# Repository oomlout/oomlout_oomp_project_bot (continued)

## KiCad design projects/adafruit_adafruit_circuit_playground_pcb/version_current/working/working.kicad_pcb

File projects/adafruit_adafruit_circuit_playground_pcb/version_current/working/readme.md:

# OOMP Project  
## Adafruit-Circuit-Playground-PCB  by adafruit  
  
oomp key: oomp_projects_flat_adafruit_adafruit_circuit_playground_pcb  
(snippet of original readme)  
  
-- Adafruit Circuit Playground Classic PCB  
<a href="http://www.adafruit.com/products/3000"><br/>  
Click here to purchase one from the Adafruit shop</a>  
  
This is the Classic version of Circuit Playground, which comes with an ATmega32u4. It's designed to be used with Arduino IDE and code.org CS Discoveries only. It even comes with Firmata already programmed in, so you can use it immediately with code.org Discoveries without any preparation or updates.  
  
If you would like to use MakeCode or CircuitPython, check out [Circuit Playground Express](http://www.adafruit.com/products/3333), which can be used with MakeCode, CircuitPython or Arduino.  
  
Circuit Playground features an ATmega32u4 processor, just like our popular Flora. The board's also round and has alligator-clip pads around it so you don't have to solder or sew to make it work. You can power it from USB, a AAA battery pack, or with a Lipoly battery (for advanced users). Just program your code into the board then take it on the go!  
  
This is the PCB files for the Adafruit **Circuit Playground Classic** (not the Express). The format is EagleCAD schematic and board layout  
- http://www.adafruit.com/products/3000  
  
**The Circuit Playground Express can be found at http://www.adafruit.com/products/3333**  
  
--- License  
  
Adafruit invests time and resources providing this open source design, please support Adafruit and open-source hardware by purchasing products from [Adafruit](https://ww  
  full source readme at [readme_src.md](readme_src.md)  
  
source repo at: [https://github.com/adafruit/Adafruit-Circuit-Playground-PCB](https://github.com/adafruit/Adafruit-Circuit-Playground-PCB)  
## Board  

## Schematic  

[schematic pdf](working_schematic.pdf)  
## Images

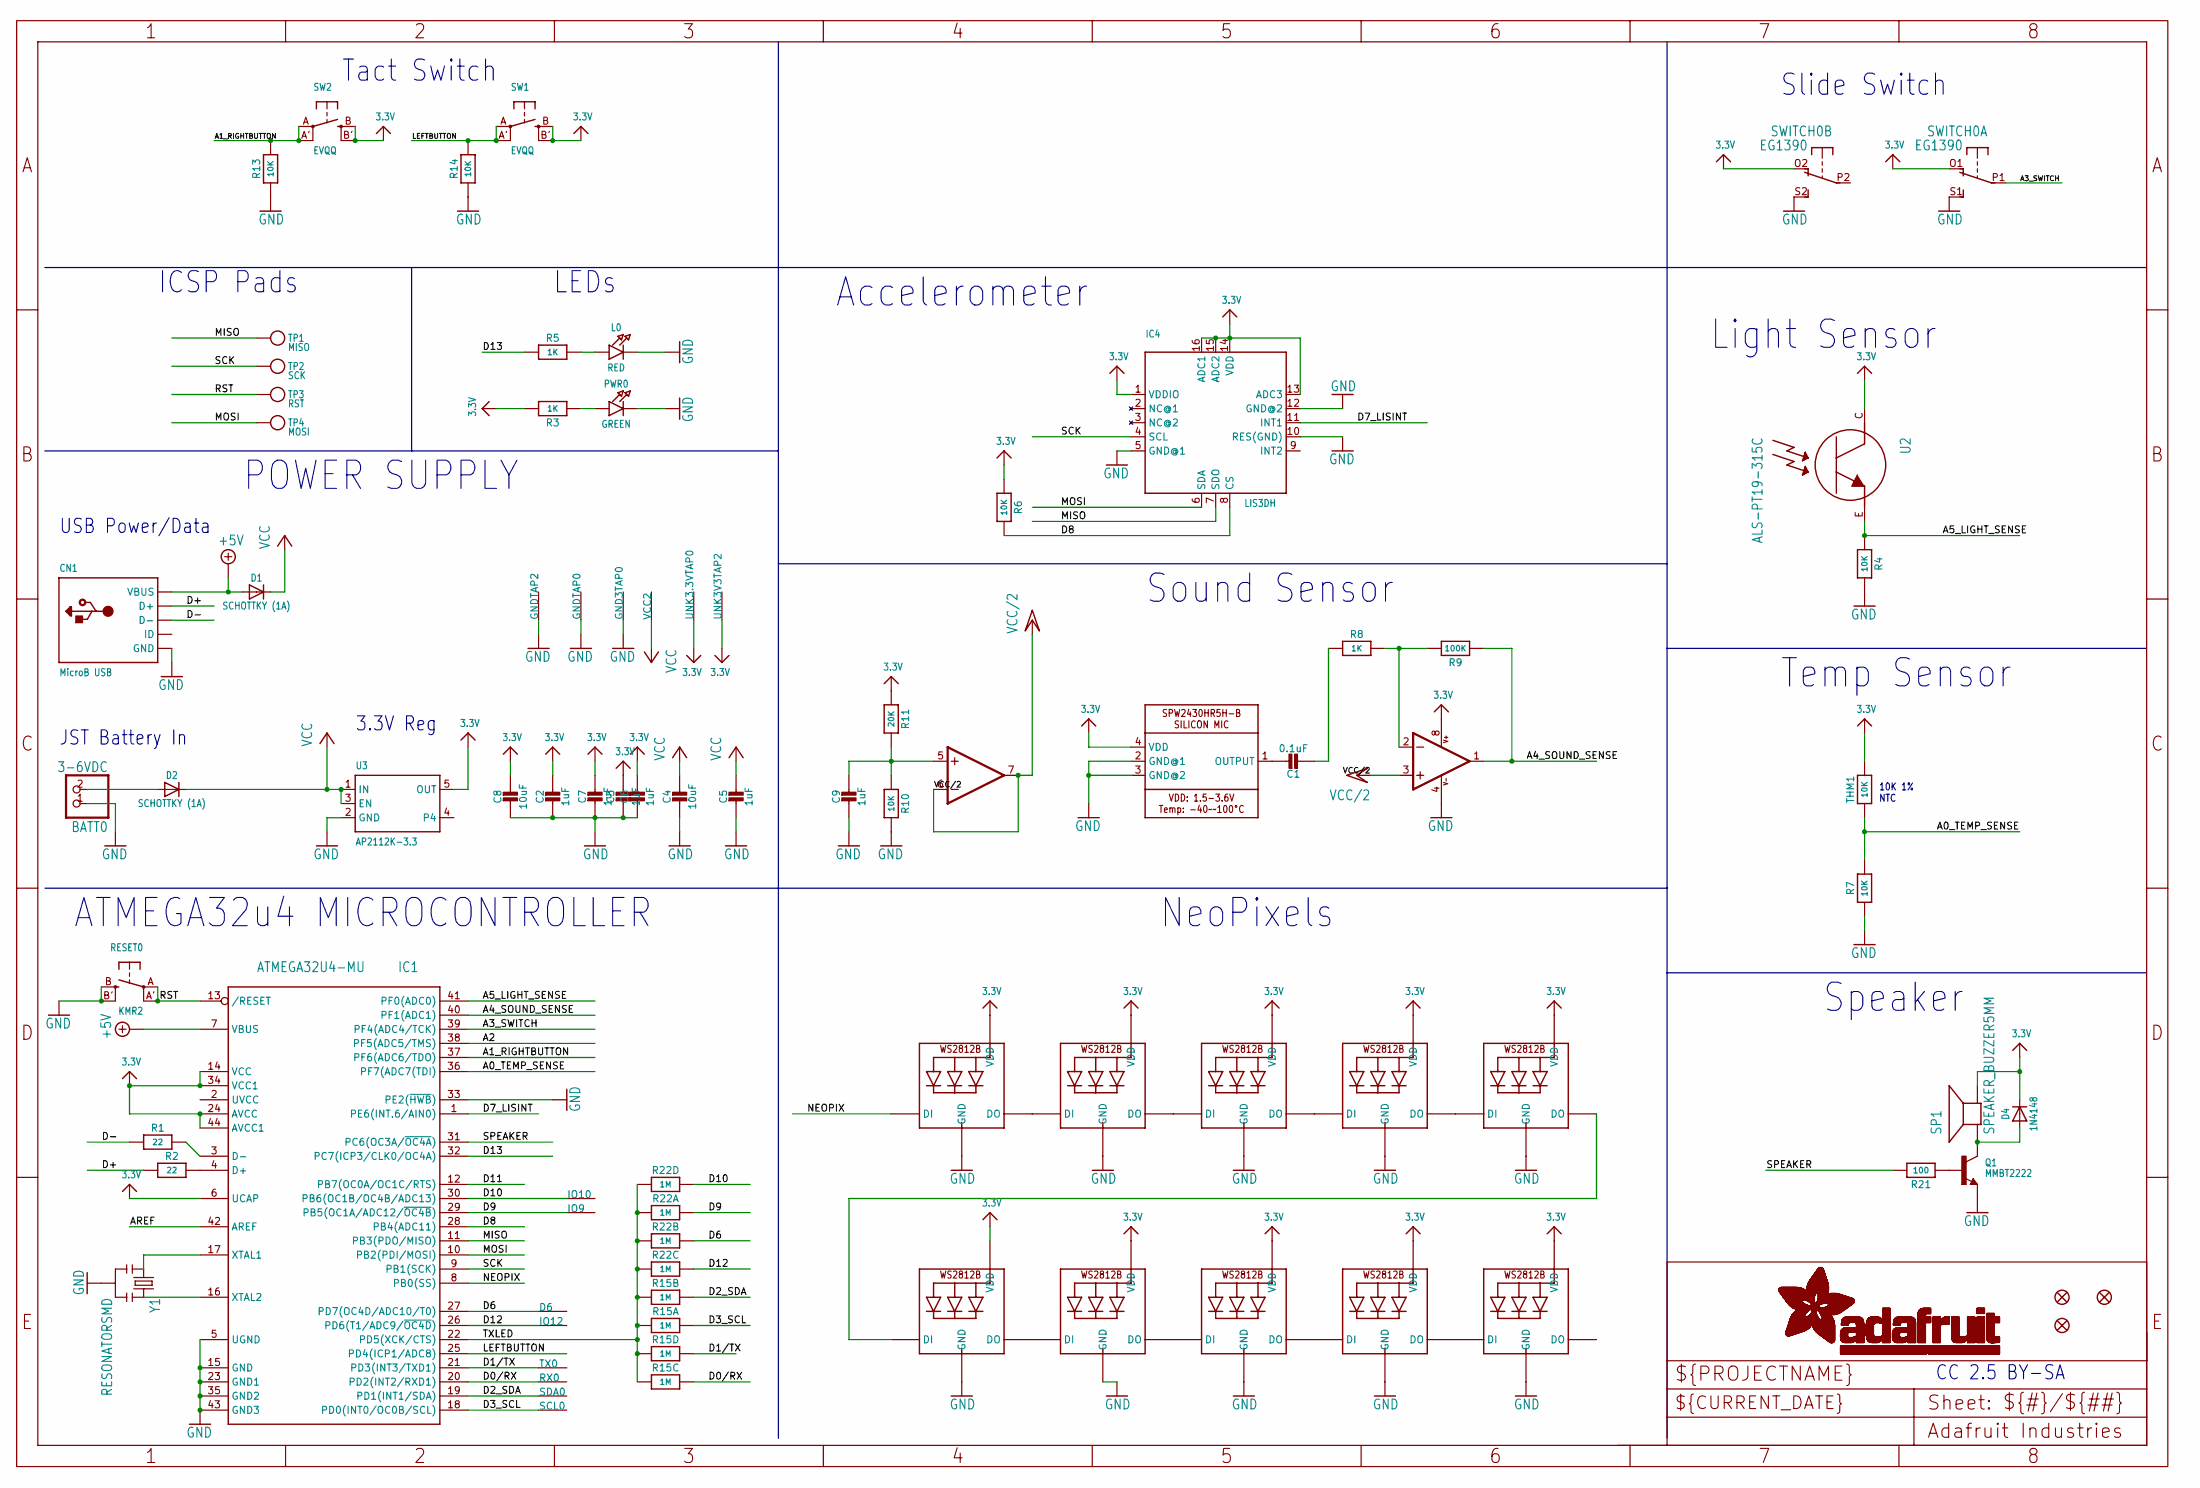
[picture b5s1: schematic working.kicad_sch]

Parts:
BATT0: 3-6VDC; JSTPH2
C1: 0.1uF; 0603-NO
C2, C3, C5, C6, C7, C9: 1uF; 0603-NO
C4, C8: 10uF; 0805-NO
CN1: MicroB USB; 4UCONN_20329_V2
D1, D2: SCHOTTKY (1A); SOD-123
D4: 1N4148; SOD-323
D6: SEWTAP-ALLIGATOR; SEWALLI
GND3TAP0: SEWTAP-ALLIGATOR; SEWALLI
GNDTAP0, GNDTAP2: SEWTAP-ALLIGATOR; SEWALLI
IC1: ATMEGA32U4-MU; TQFN44_7MM
IC2: LMV358?MM; MSOP08
IC4: LIS3DH; LGA16_3X3MM
IO9, IO10, IO12: SEWTAP-ALLIGATOR; SEWALLI
L0: RED; CHIPLED_0805_NOOUTLINE
LED1, LED2, LED3, LED4, LED5, LED6, LED7, LED8, LED9, LED10: WS2812B3535; LED3535
PWR0: GREEN; CHIPLED_0805_NOOUTLINE
Q1: MMBT2222; SOT23-WIDE
R1, R2: 22; 0603-NO
R3, R5, R8: 1K; 0603-NO
R4, R6, R7, R10, R13, R14: 10K; 0603-NO
R9: 100K; 0603-NO
R11: 20K; 0603-NO
R15, R22: 1M; RESPACK_4X0603_NO
R21: 100; 0603-NO
RESET0: KMR2; BTN_KMR2_4.6X2.8
RX0: SEWTAP-ALLIGATOR; SEWALLI
SCL0: SEWTAP-ALLIGATOR; SEWALLI
SDA0: SEWTAP-ALLIGATOR; SEWALLI
SP1: SPEAKER_BUZZER5MM; BUZZER_SMT_5MM
SW1, SW2: EVQQ; EVQ-Q2_SMALLER
SWITCH0: EG1390
THM1: 10K; _0402
TP1: MISO; TESTPOINT_ROUND_1.5MM
TP2: SCK; TESTPOINT_ROUND_1.5MM
TP3: RST; TESTPOINT_ROUND_1.5MM
TP4: MOSI; TESTPOINT_ROUND_1.5MM
TX0: SEWTAP-ALLIGATOR; SEWALLI
U1: SPW2430; SPW2430HR5H-B
U2: ALS-PT19-315C
U3: AP2112K-3.3; SOT23-5
U$2, U$3, U$6: FIDUCIAL""; FIDUCIAL_1MM
UNK3.3VTAP0, UNK3V3TAP2: SEWTAP-ALLIGATOR; SEWALLI
VCC2: SEWTAP-ALLIGATOR; SEWALLI
Y1: RESONATORSMD; RESONATOR-SMD

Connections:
3.3V: C2.1, C3.1, C6.1, C7.1, C8.1, D4.C, IC1.6 (UCAP), IC1.14 (VCC), IC1.24 (AVCC), IC1.34 (VCC1), IC1.44 (AVCC1), IC2.8 (V+), IC4.1 (VDDIO), IC4.13 (ADC3), IC4.14 (VDD), IC4.15 (ADC2), IC4.16 (ADC1), LED1.2 (VDD), LED2.2 (VDD), LED3.2 (VDD), LED4.2 (VDD), LED5.2 (VDD), LED6.2 (VDD), LED7.2 (VDD), LED8.2 (VDD), LED9.2 (VDD), LED10.2 (VDD), R3.2, R6.1, R11.1, SP1.-, SW1.B (S), SW1.B' (S1), SW2.B (S), SW2.B' (S1), SWITCH0.O1 (O), SWITCH0.O2 (O), THM1.2, U1.4 (VDD), U2.C, U3.5 (OUT), UNK3.3VTAP0.P$1, UNK3V3TAP2.P$1
+5V: CN1.VBUS, D1.A, IC1.7 (VBUS)
A0_TEMP_SENSE: IC1.36 (PF7(ADC7(TDI)), R7.2, THM1.1
A1_RIGHTBUTTON: IC1.37 (PF6(ADC6/TDO)), R13.2, SW2.A, SW2.A' (P1)
A2: IC1.38 (PF5(ADC5/TMS))
A3_SWITCH: IC1.39 (PF4(ADC4/TCK)), SWITCH0.P1
A4_SOUND_SENSE: IC1.40 (PF1(ADC1)), IC2.1 (OUT), R9.1
A5_LIGHT_SENSE: IC1.41 (PF0(ADC0)), R4.2, U2.E
AREF: IC1.42 (AREF)
D0/RX: IC1.20 (PD2(INT2/RXD1)), R15.6 (2), RX0.P$1
D1/TX: IC1.21 (PD3(INT3/TXD1)), R15.5 (2), TX0.P$1
D2_SDA: IC1.19 (PD1(INT1/SDA)), R15.7 (2), SDA0.P$1
D3_SCL: IC1.18 (PD0(INT0/OC0B/SCL)), R15.8 (2), SCL0.P$1
D6: D6.P$1, IC1.27 (PD7(OC4D/ADC10/T0)), R22.7 (2)
D7_LISINT: IC1.1 (PE6(INT.6/AIN0)), IC4.11 (INT1)
D8: IC1.28 (PB4(ADC11)), IC4.8 (CS), R6.2
D9: IC1.29 (PB5(OC1A/ADC12/~OC4B)), IO9.P$1, R22.8 (2)
D10: IC1.30 (PB6(OC1B/OC4B/ADC13)), IO10.P$1, R22.5 (2)
D11: IC1.12 (PB7(OC0A/OC1C/RTS))
D12: IC1.26 (PD6(T1/ADC9/~OC4D)), IO12.P$1, R22.6 (2)
D13: IC1.32 (PC7(ICP3/CLK0/OC4A)), R5.1
D+: CN1.D+, R2.1
D-: CN1.D-, R1.1
GND: BATT0.1, C2.2, C3.2, C4.2, C5.2, C6.2, C7.2, C8.2, C9.2, CN1.BASE@1 (GND), CN1.BASE@2 (GND), CN1.GND, CN1.SPRT@1 (GND), CN1.SPRT@2 (GND), CN1.SPRT@3 (GND), CN1.SPRT@4 (GND), GND3TAP0.P$1, GNDTAP0.P$1, GNDTAP2.P$1, IC1.5 (UGND), IC1.15 (GND), IC1.23 (GND1), IC1.33 (PE2(~HWB)), IC1.35 (GND2), IC1.43 (GND3), IC2.4 (V-), IC4.5 (GND@1), IC4.10 (RES(GND)), IC4.12 (GND@2), L0.C, LED1.4 (GND), LED2.4 (GND), LED3.4 (GND), LED4.4 (GND), LED5.4 (GND), LED6.4 (GND), LED7.4 (GND), LED8.4 (GND), LED9.4 (GND), LED10.4 (GND), PWR0.C, Q1.2 (E), R4.1, R7.1, R10.2, R13.1, R14.1, RESET0.B (S), RESET0.B' (S1), SWITCH0.S1 (S), SWITCH0.S2 (S), U1.2 (GND@1), U1.3 (GND@2), U3.2 (GND), Y1.2
LEFTBUTTON: IC1.25 (PD4(ICP1/ADC8)), R14.2, SW1.A, SW1.A' (P1)
MISO: IC1.11 (PB3(PDO/MISO)), IC4.7 (SDO), TP1.P$1
MOSI: IC1.10 (PB2(PDI/MOSI)), IC4.6 (SDA), TP4.P$1
unnamed: PWR0.A, R3.1
unnamed: IC2.2 (-IN), R8.2, R9.2
unnamed: IC1.3 (D-), R1.2
unnamed: IC1.4 (D+), R2.2
unnamed: C9.1, IC2.5 (+IN), R10.1, R11.2
unnamed: BATT0.2, D2.A
unnamed: IC1.17 (XTAL1), Y1.1
unnamed: IC1.16 (XTAL2), Y1.3
unnamed: L0.A, R5.2
unnamed: LED1.1 (DI), LED2.3 (DO)
unnamed: LED1.3 (DO), LED3.1 (DI)
unnamed: LED2.1 (DI), LED10.3 (DO)
unnamed: LED6.3 (DO), LED7.1 (DI)
unnamed: C1.2, R8.1
unnamed: LED7.3 (DO), LED8.1 (DI)
unnamed: LED8.3 (DO), LED9.1 (DI)
unnamed: LED9.3 (DO), LED10.1 (DI)
unnamed: LED3.3 (DO), LED4.1 (DI)
unnamed: LED4.3 (DO), LED5.1 (DI)
unnamed: D4.A, Q1.3 (C), SP1.+
unnamed: Q1.1 (B), R21.1
NEOPIX: IC1.8 (PB0(SS)), LED6.1 (DI)
RST: IC1.13 (/RESET), RESET0.A, RESET0.A' (P1), TP3.P$1
SCK: IC1.9 (PB1(SCK)), IC4.4 (SCL), TP2.P$1
SOUNDOUT: C1.1, U1.1 (OUTPUT)
SPEAKER: IC1.31 (PC6(OC3A/~OC4A)), R21.2
TXLED: IC1.22 (PD5(XCK/CTS)), R15.1, R15.2 (1), R15.3 (1), R15.4 (1), R22.1, R22.2 (1), R22.3 (1), R22.4 (1)
VCC: C4.1, C5.1, D1.C, D2.C, U3.1 (IN), U3.3 (EN), VCC2.P$1
VCC/2: IC2.3 (+IN), IC2.6 (-IN), IC2.7 (OUT)

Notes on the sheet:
Accelerometer
Slide Switch
Sound Sensor
NeoPixels
USB Power/Data
CC 2.5 BY-SA
Temp Sensor
Light Sensor
ATMEGA32u4 MICROCONTROLLER
Tact Switch
Speaker
3.3V Reg
10K 1% NTC
JST Battery In
POWER SUPPLY
LEDs
ICSP Pads

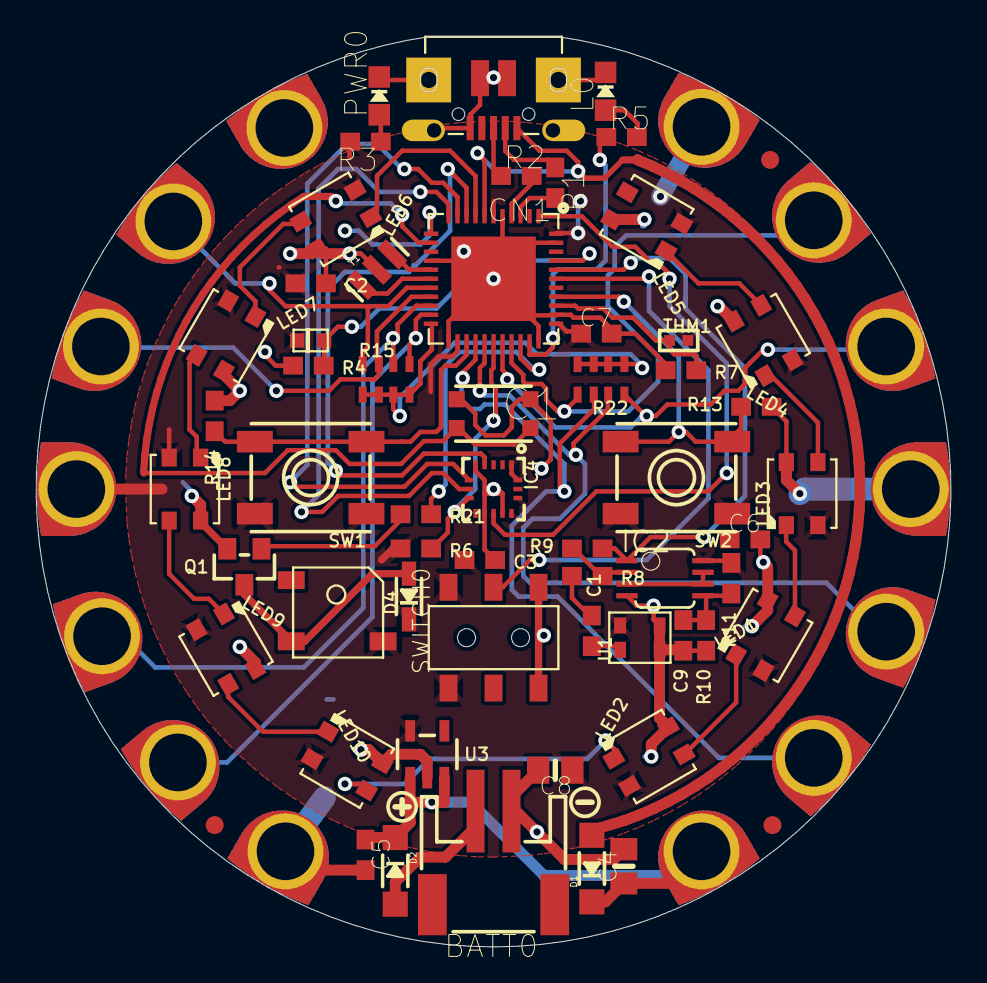
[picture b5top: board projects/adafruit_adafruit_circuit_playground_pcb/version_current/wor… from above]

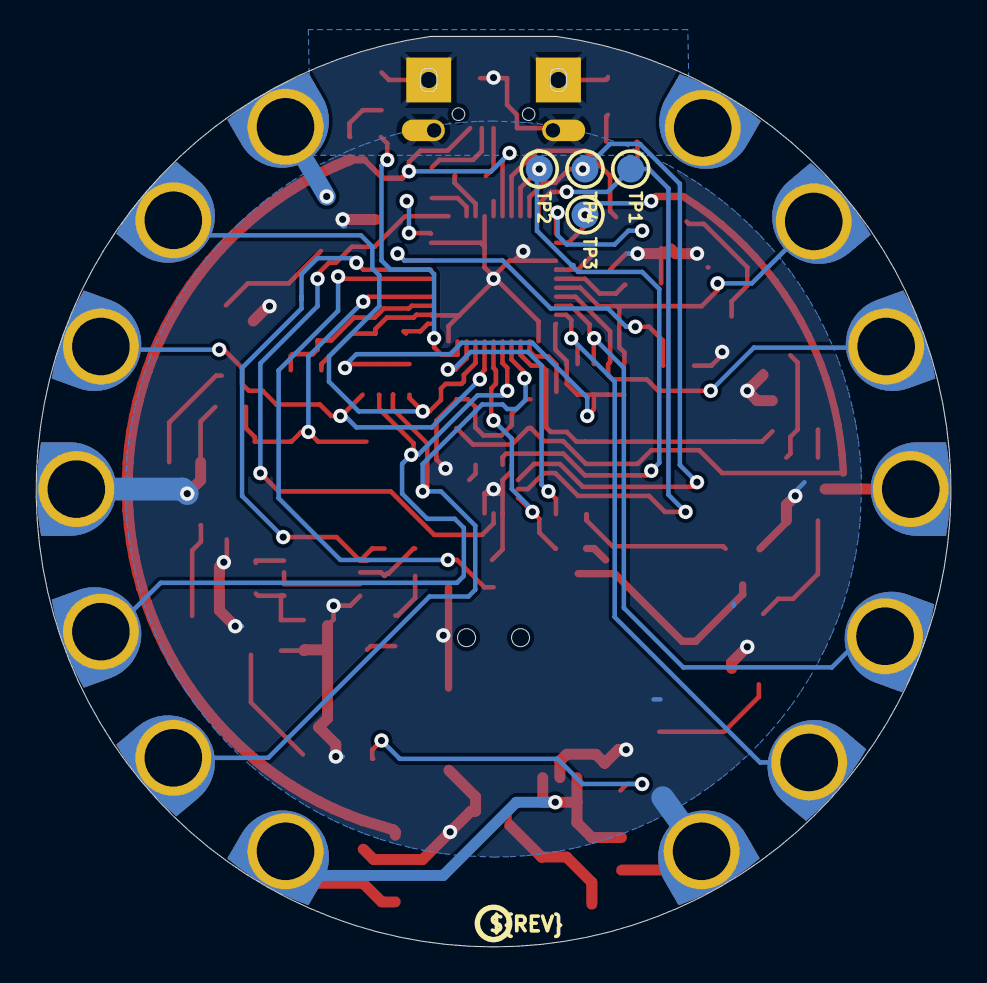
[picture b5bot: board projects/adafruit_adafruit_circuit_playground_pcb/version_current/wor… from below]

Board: 16 copper layers, 50.8 x 50.6 mm, 83 parts (7 on the bottom side), 53 nets.

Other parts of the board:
U$1: SYMBOL_MINUS
U$4: FLORAMED
U$7: PCBFEAT-REV-040
U$34: CPLAYFRONT
U$35: SYMBOL_PLUS
U$46: CPLAYBACK

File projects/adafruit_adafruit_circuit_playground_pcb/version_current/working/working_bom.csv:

Row,Description,Part,References,Value,Footprint,Quantity Per PCB,Status,Datasheet,BOM
1,,CON_JST_PH_2PIN,BATT0,3-6VDC,JSTPH2,1, ,,
2,,CAP_CERAMIC0603_NO,C1,0.1uF,0603-NO,1, ,,
3,,CAP_CERAMIC0603_NO,C2 C3 C5 C6 C7 C9,1uF,0603-NO,6, ,,
4,,CAP_CERAMIC0805-NOOUTLINE,C4 C8,10uF,0805-NO,2, ,,
5,,USB_MICRO_20329_V2,CN1,MicroB USB,4UCONN_20329_V2,1, ,,
6,,DIODESOD-323,D4,1N4148,SOD-323,1, ,,
7,,DIODESOD-123,D1 D2,SCHOTTKY (1A),SOD-123,2, ,,
8,,SEWTAP-ALLIGATOR,D6 GND3TAP0 GNDTAP0 GNDTAP2 IO9 IO10 IO12 RX0 SCL0 SDA0 TX0 UNK3.3VTAP0 UNK3V3TAP2 VCC2,SEWTAP-ALLIGATOR,SEWALLI,14, ,,
9,,ATMEGA32U4-MU,IC1,ATMEGA32U4-MU,TQFN44_7MM,1, ,,
10,,ACCEL_LIS3DHTR,IC4,LIS3DH,LGA16_3X3MM,1, ,,
11,,LMV358?MM,IC2,LMV358?MM,MSOP08,1, ,,
12,,LED0805_NOOUTLINE,L0,RED,CHIPLED_0805_NOOUTLINE,1, ,,
13,,WS2812B3535,LED1 LED2 LED3 LED4 LED5 LED6 LED7 LED8 LED9 LED10,WS2812B3535,LED3535,10, ,,
14,,LED0805_NOOUTLINE,PWR0,GREEN,CHIPLED_0805_NOOUTLINE,1, ,,
15,,TRANSISTOR_NPNWIDE,Q1,MMBT2222,SOT23-WIDE,1, ,,
16,,RESISTOR_0603_NOOUT,R1 R2,22,0603-NO,2, ,,
17,,RESISTOR_0603_NOOUT,R21,100,0603-NO,1, ,,
18,,RESISTOR_0603_NOOUT,R3 R5 R8,1K,0603-NO,3, ,,
19,,RESISTOR_0603_NOOUT,R4 R6 R7 R10 R13 R14,10K,0603-NO,6, ,,
20,,RESISTOR_0603_NOOUT,R11,20K,0603-NO,1, ,,
21,,RESISTOR_0603_NOOUT,R9,100K,0603-NO,1, ,,
22,,RESISTOR_4PACK_NO,R15 R22,1M,RESPACK_4X0603_NO,2, ,,
23,,SWITCH_TACT_SMT4.6X2.8,RESET0,KMR2,BTN_KMR2_4.6X2.8,1, ,,
24,,SPEAKER_BUZZER5MM,SP1,SPEAKER_BUZZER5MM,BUZZER_SMT_5MM,1, ,,
25,,SWITCH_TACT_SMT_EVQQ2_SMALL,SW1 SW2,EVQQ,EVQ-Q2_SMALLER,2, ,,
26,,DPDT-EG1390,SWITCH0,EG1390,EG1390,1, ,,
27,,RESISTOR_0402,THM1,10K,_0402,1, ,,
28,,LIGHT_ALS-PT19-315C,U2,ALS-PT19-315C,ALS-PT19-315C,1, ,,
29,,VREG_SOT23-5,U3,AP2112K-3.3,SOT23-5,1, ,,
30,,SPW2430HR5H-B,U1,SPW2430,SPW2430HR5H-B,1, ,,
31,,RESONATORSMD,Y1,RESONATORSMD,RESONATOR-SMD,1, ,,





Project info:
Schematic:,working
Variant:,default
Revision:,
Date:,2023-08-02_17-08-32
KiCad Version:,7.0.6-7.0.6~ubuntu22.04.1
Statistics:
Component Groups:,31
Component Count:,70 (0 SMD/ 0 THT)
Fitted Components:,70 (0 SMD/ 0 THT)
Number of PCBs:,1
Total Components:,70

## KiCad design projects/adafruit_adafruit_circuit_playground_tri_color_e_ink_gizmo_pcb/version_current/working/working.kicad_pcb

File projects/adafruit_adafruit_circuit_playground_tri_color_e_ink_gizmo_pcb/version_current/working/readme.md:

# Adafruit-Circuit-Playground-Tri-Color-E-Ink-Gizmo-PCB by adafruit  
This is a harvested standardized copy of a project from github.  
The original project can be found at:  
https://github.com/adafruit/Adafruit-Circuit-Playground-Tri-Color-E-Ink-Gizmo-PCB  
Please consult that link for additional, details, files, and license information.  
Note: It was auto harvested and if the original repo had more than one board file or anything out of the ordinary the files here are likely not representative.

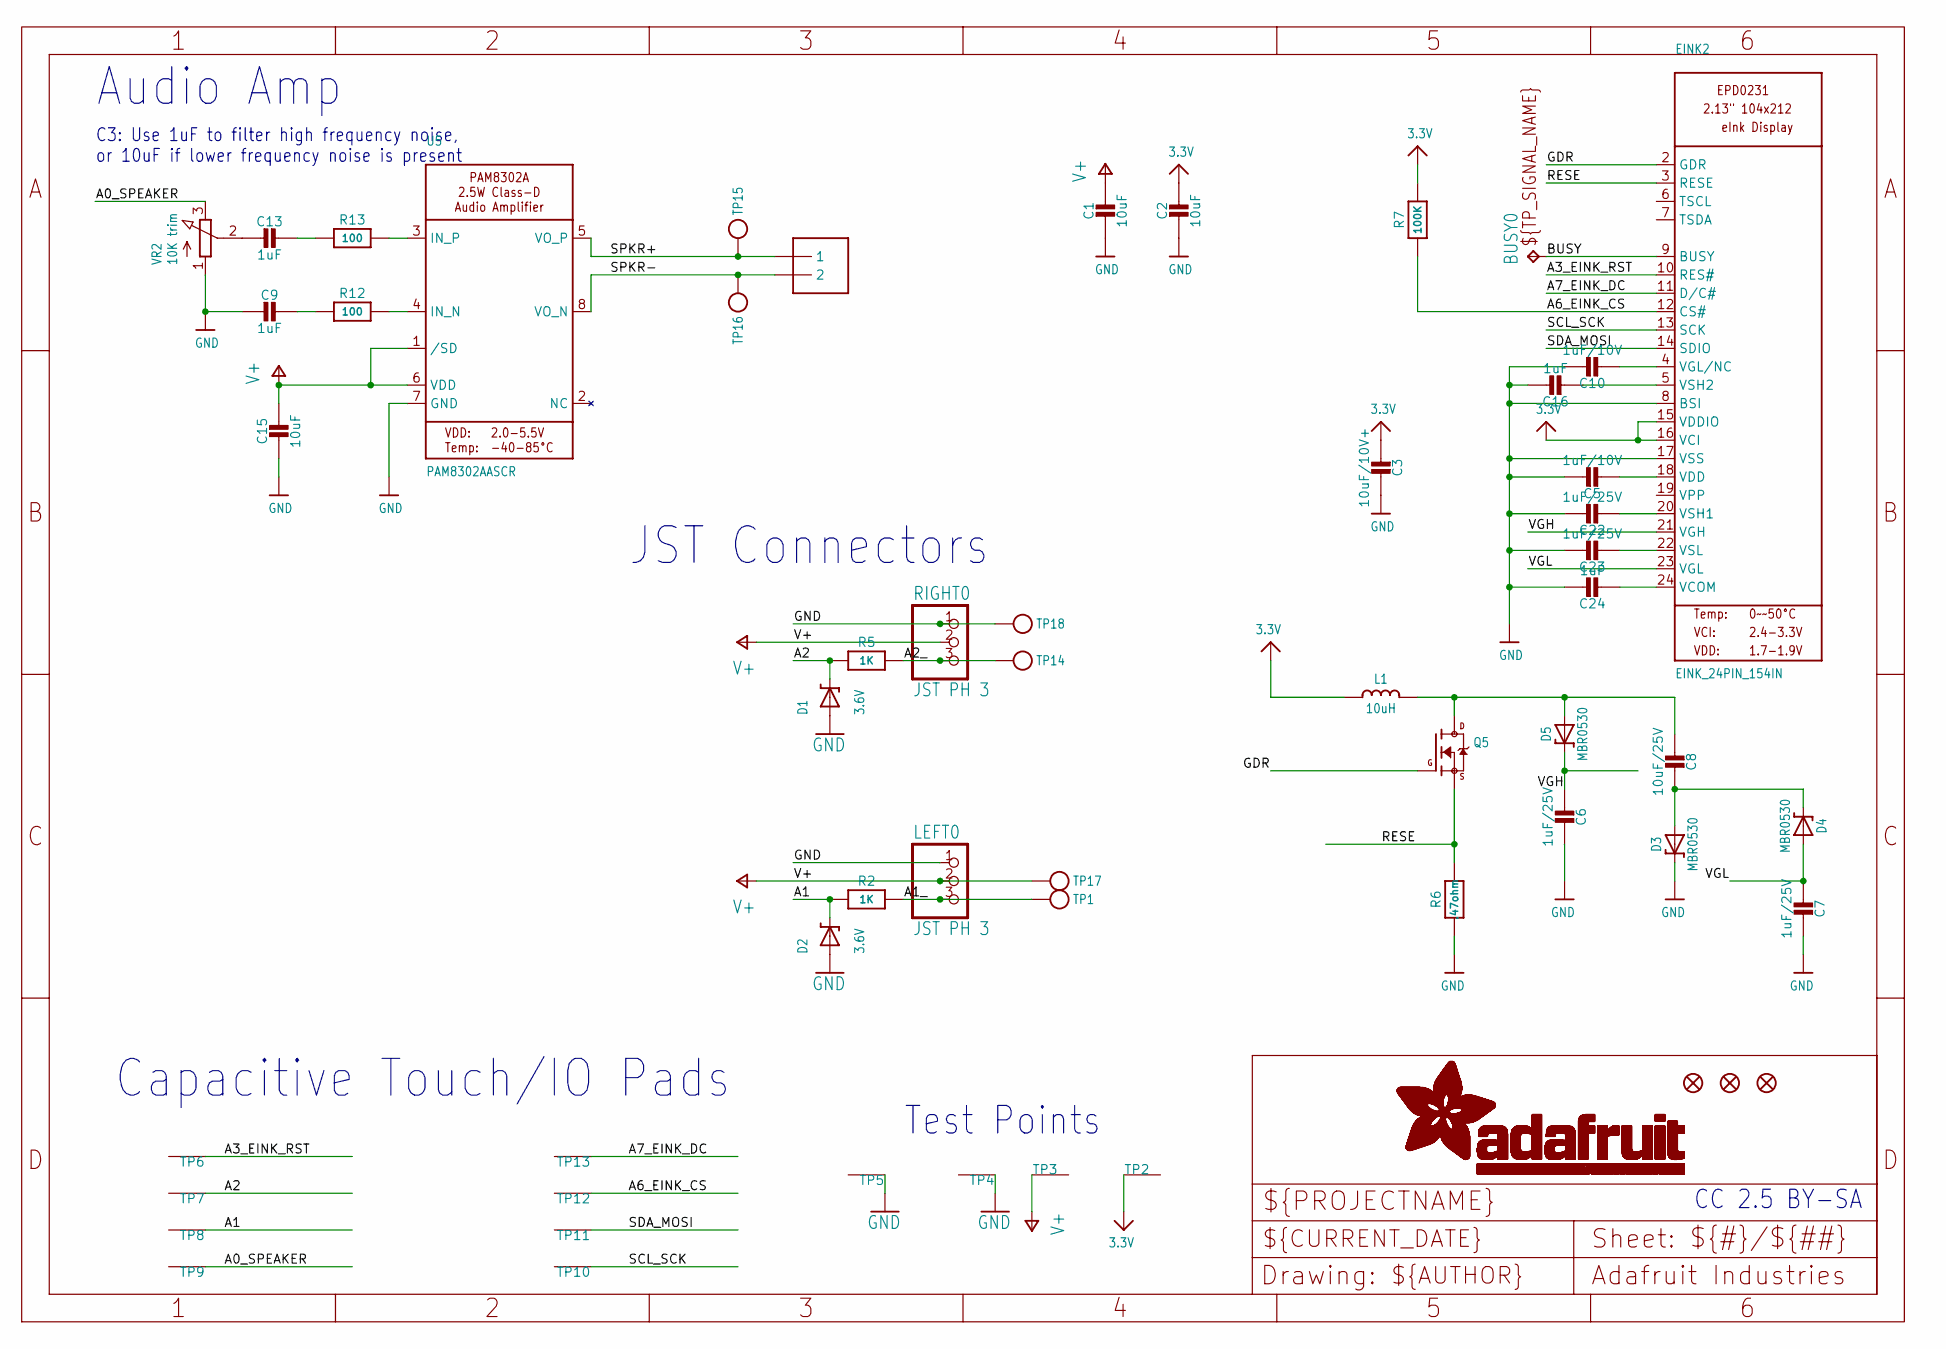
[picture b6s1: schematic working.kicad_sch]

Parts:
BUSY0: TPTP15SQ; TP15SQ
C1, C2, C15: 10uF; 0805-NO
C3: 10uF/10V+; 0805-NO
C5, C10: 1uF/10V; 0805-NO
C6, C7, C22, C23: 1uF/25V; 0805-NO
C8: 10uF/25V; 0805-NO
C9, C13, C16, C24: 1uF; 0805-NO
D1, D2: 3.6V; SOD-323
D3, D4, D5: MBR0530; SOD-123
EINK2: EINK_24PIN_154IN; EINK_154IN
L1: 10uH; INDUCTOR_4X4MM_NR401
LEFT0: JST PH 3; JSTPH3
Q5: IRLML2060TRPBF; SOT23-3
R2, R5: 1K; 0603-NO
R6: .47ohm; 0805_10MGAP
R7: 100K; 0603-NO
R12, R13: 100; 0603-NO
RIGHT0: JST PH 3; JSTPH3
TP1, TP14, TP15, TP16, TP17, TP18: TESTPOINTROUND1.5MMNO; TESTPOINT_ROUND_1.5MM_NO
TP2, TP3, TP4, TP5, TP6, TP7, TP8, TP9, TP10, TP11, TP12, TP13: SEWTAP_SMTNUTM3; SMT_NUT_3MM
U5: PAM8302AASCR; MSOP8_0.65MM
U$1: CON_MOLEX_2P; 53398-0271
U$2, U$3, U$6: FIDUCIAL_1MM
VR2: 10K trim; TRIMPOT_BOURNS_3303W

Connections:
3.3V: C2.1, C3.2, EINK2.15 (VDDIO), EINK2.16 (VCI), L1.P$2 (2), R7.2, TP2.P$1
A0_SPEAKER: TP9.P$1, VR2.3 (E)
A1: D2.C, R2.2, TP8.P$1
A1_: LEFT0.3, R2.1, TP1.P$1
A2: D1.C, R5.2, TP7.P$1
A2_: R5.1, RIGHT0.3, TP14.P$1
A3_EINK_RST: EINK2.10 (RES#), TP6.P$1
A6_EINK_CS: EINK2.12 (CS#), R7.1, TP12.P$1
A7_EINK_DC: EINK2.11 (D/C#), TP13.P$1
BUSY: BUSY0.TP, EINK2.9 (BUSY)
GDR: EINK2.2 (GDR), Q5.1 (G)
GND: C1.2, C2.2, C3.1, C5.1, C6.2, C7.2, C9.2, C10.1, C15.2, C16.1, C22.1, C23.1, C24.1, D1.A, D2.A, D3.C, EINK2.8 (BSI), EINK2.17 (VSS), LEFT0.1, R6.2, RIGHT0.1, TP4.P$1, TP5.P$1, TP18.P$1, U5.7 (GND), VR2.1 (A)
unnamed: C8.2, D3.A, D4.C
unnamed: C8.1, D5.A, L1.P$1 (1), Q5.3 (D)
unnamed: C16.2, EINK2.5 (VSH2)
unnamed: C5.2, EINK2.18 (VDD)
unnamed: C22.2, EINK2.20 (VSH1)
unnamed: C10.2, EINK2.4 (VGL/NC)
unnamed: R12.2, U5.4 (IN_N)
unnamed: R13.2, U5.3 (IN_P)
unnamed: C9.1, R12.1
unnamed: C13.1, R13.1
unnamed: C13.2, VR2.2 (S)
unnamed: C23.2, EINK2.22 (VSL)
unnamed: C24.2, EINK2.24 (VCOM)
RESE: EINK2.3 (RESE), Q5.2 (S), R6.1
SCL_SCK: EINK2.13 (SCK), TP10.P$1
SDA_MOSI: EINK2.14 (SDIO), TP11.P$1
SPKR+: TP15.P$1, U5.5 (VO_P), U$1.1
SPKR-: TP16.P$1, U5.8 (VO_N), U$1.2
V+: C1.1, C15.1, LEFT0.2, RIGHT0.2, TP3.P$1, TP17.P$1, U5.1 (/SD), U5.6 (VDD)
VGH: C6.1, D5.C, EINK2.21 (VGH)
VGL: C7.1, D4.A, EINK2.23 (VGL)

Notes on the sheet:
C3: Use 1uF to filter high frequency noise, or 10uF if lower frequency noise is present
Capacitive Touch/IO Pads
Test Points
Audio Amp
JST Connectors
CC 2.5 BY-SA

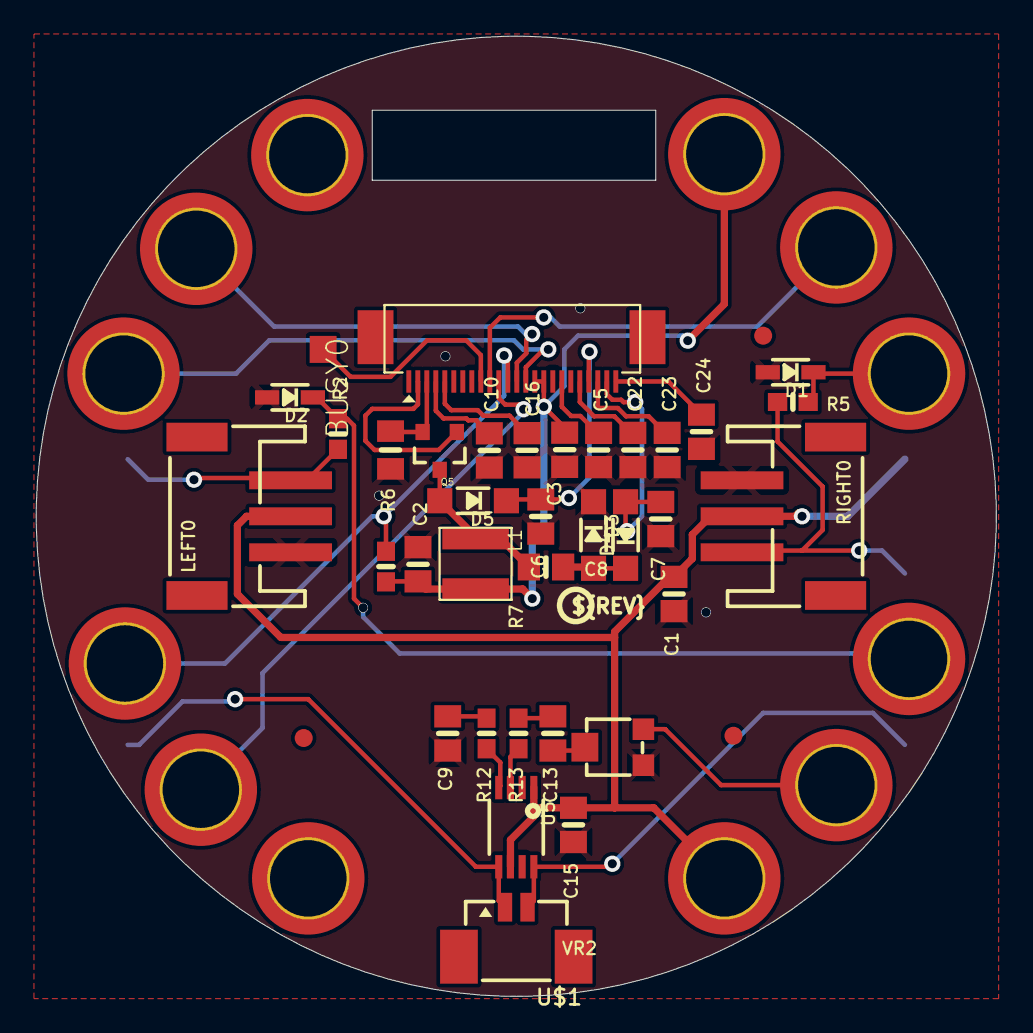
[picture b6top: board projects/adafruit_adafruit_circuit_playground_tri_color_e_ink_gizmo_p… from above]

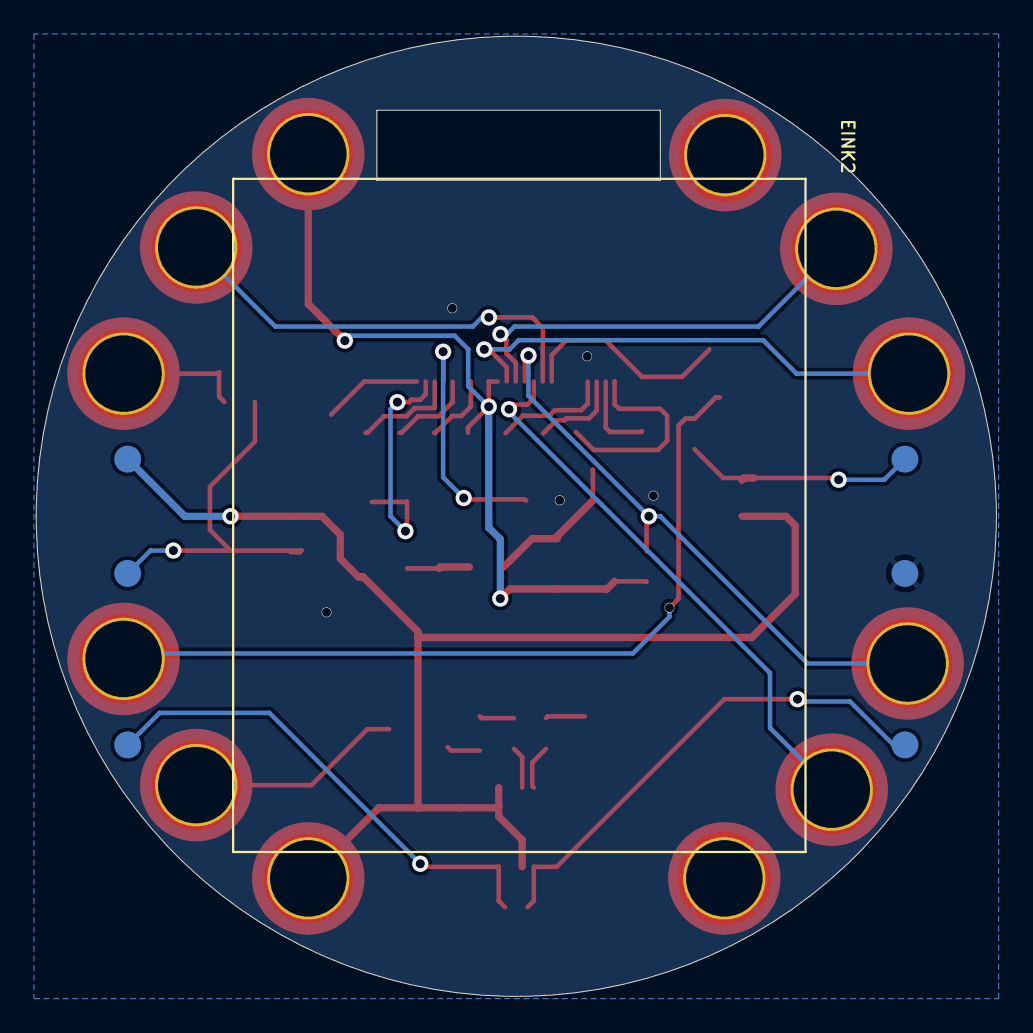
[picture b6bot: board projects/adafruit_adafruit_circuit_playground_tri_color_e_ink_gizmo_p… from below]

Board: 16 copper layers, 53.3 x 53.3 mm, 59 parts (8 on the bottom side), 33 nets.

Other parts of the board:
U$4: EINKGIZMO_BACK
U$7: PCBFEAT-REV-040
U$8: EINKGIZMO_FRONT

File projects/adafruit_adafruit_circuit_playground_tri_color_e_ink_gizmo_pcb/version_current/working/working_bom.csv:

Row,Description,Part,References,Value,Footprint,Quantity Per PCB,Status,Datasheet,BOM
1,,TPTP15SQ,BUSY0,TPTP15SQ,TP15SQ,1, ,,
2,,CAP_CERAMIC0805-NOOUTLINE,C9 C13 C16 C24,1uF,0805-NO,4, ,,
3,,CAP_CERAMIC0805-NOOUTLINE,C1 C2 C15,10uF,0805-NO,3, ,,
4,,CAP_CERAMIC0805-NOOUTLINE,C3,10uF/10V+,0805-NO,1, ,,
5,,CAP_CERAMIC0805-NOOUTLINE,C8,10uF/25V,0805-NO,1, ,,
6,,CAP_CERAMIC0805-NOOUTLINE,C5 C10,1uF/10V,0805-NO,2, ,,
7,,CAP_CERAMIC0805-NOOUTLINE,C6 C7 C22 C23,1uF/25V,0805-NO,4, ,,
8,,DIODE-ZENERSOD323,D1 D2,3.6V,SOD-323,2, ,,
9,,DIODE-SCHOTTKYSOD-123,D3 D4 D5,MBR0530,SOD-123,3, ,,
10,,EINK_24PIN_154IN,EINK2,EINK_24PIN_154IN,EINK_154IN,1, ,,
11,,INDUCTORNR401,L1,10uH,INDUCTOR_4X4MM_NR401,1, ,,
12,,CON_JST_PH_3PIN,LEFT0 RIGHT0,JST PH 3,JSTPH3,2, ,,
13,,IRLML2060TRPBF,Q5,IRLML2060TRPBF,SOT23-3,1, ,,
14,,RESISTOR0805_10MGAP,R6,.47ohm,0805_10MGAP,1, ,,
15,,RESISTOR_0603_NOOUT,R12 R13,100,0603-NO,2, ,,
16,,RESISTOR_0603_NOOUT,R2 R5,1K,0603-NO,2, ,,
17,,RESISTOR_0603_NOOUT,R7,100K,0603-NO,1, ,,
18,,AUDIOAMP_PAM8302A,U5,PAM8302AASCR,MSOP8_0.65MM,1, ,,
19,,CON_MOLEX_2P,U$1,CON_MOLEX_2P,53398-0271,1, ,,
20,,TRIMPOT3303W/X,VR2,10K trim,TRIMPOT_BOURNS_3303W,1, ,,





Project info:
Schematic:,working
Variant:,default
Revision:,
Date:,2023-08-02_17-08-32
KiCad Version:,7.0.6-7.0.6~ubuntu22.04.1
Statistics:
Component Groups:,20
Component Count:,35 (0 SMD/ 0 THT)
Fitted Components:,35 (0 SMD/ 0 THT)
Number of PCBs:,1
Total Components:,35
